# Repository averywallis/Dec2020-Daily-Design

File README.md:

# Dec2020-Daily-Design
Attempt at daily designs in December 2020. Expect very unfinished design, some with potentially massive issues

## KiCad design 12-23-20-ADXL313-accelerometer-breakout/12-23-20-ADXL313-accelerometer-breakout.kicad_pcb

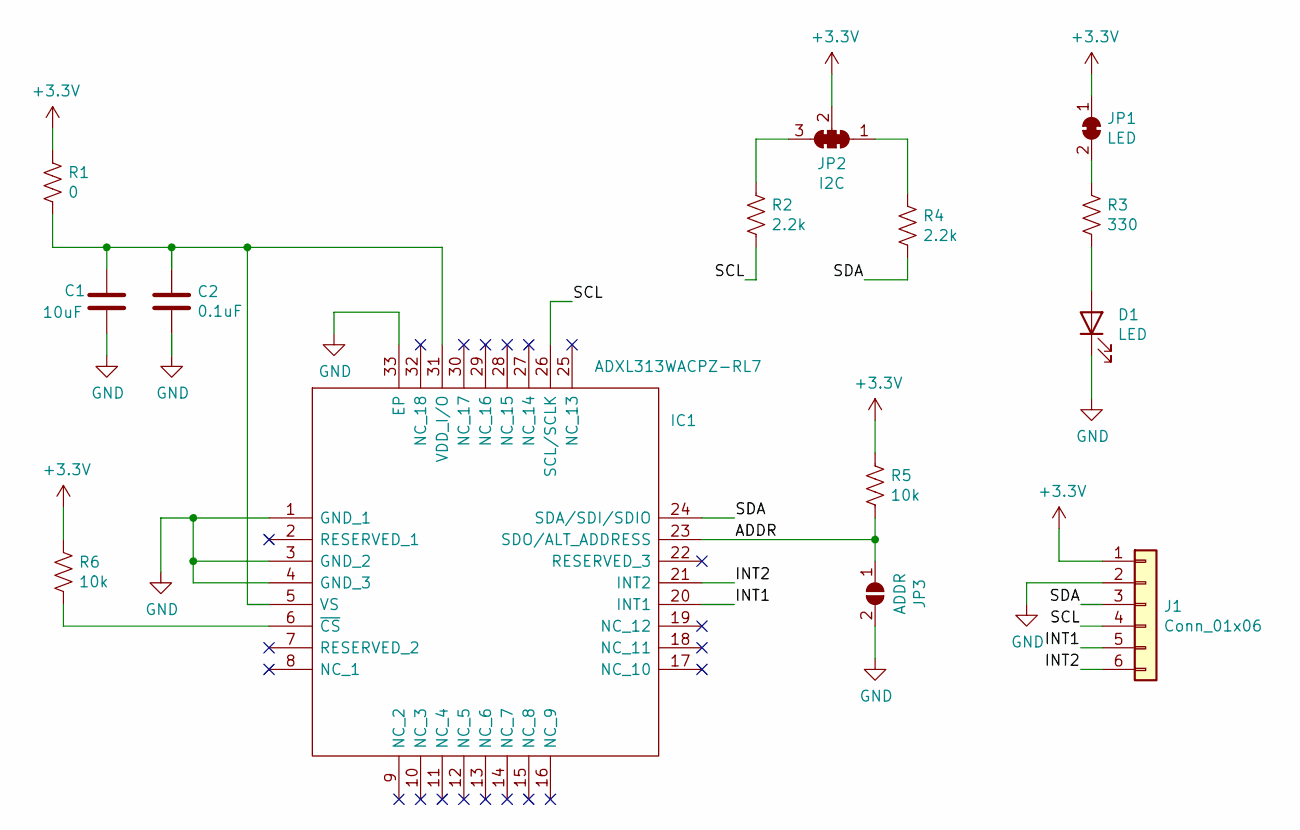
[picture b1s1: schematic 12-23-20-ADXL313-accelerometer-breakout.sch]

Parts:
C1: 10uF; C_0805_2012Metric
C2: 0.1uF; C_0805_2012Metric
D1: LED; LED_0805_2012Metric
IC1: ADXL313WACPZ-RL7; QFN50P500X500X155-33N-D; Manufacturer_Part_Number ADXL313WACPZ-RL7; Mouser Part Number 584-ADXL313WACPZ-RL7
J1: Conn_01x06; PinHeader_1x06_P2.54mm_Vertical
JP1: LED; SolderJumper-2_P1.3mm_Bridged_RoundedPad1.0x1.5mm
JP2: I2C; SMT-JUMPER_3_2-NC_TRACE_SILK
JP3: ADDR; SolderJumper-2_P1.3mm_Open_RoundedPad1.0x1.5mm
R1: 0; R_0805_2012Metric
R2, R4: 2.2k; R_0805_2012Metric
R3: 330; R_0805_2012Metric
R5, R6: 10k; R_0805_2012Metric

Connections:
+3V3: J1.1, JP1.1 (A), JP2.2 (C), R1.1, R5.1, R6.1
/ADDR: IC1.23 (SDO/ALT_ADDRESS), JP3.1 (A), R5.2
/INT1: IC1.20 (INT1), J1.5
/INT2: IC1.21 (INT2), J1.6
/SCL: IC1.26 (SCL/SCLK), J1.4, R2.2
/SDA: IC1.24 (SDA/SDI/SDIO), J1.3, R4.2
GND: C1.2, C2.2, D1.1 (K), IC1.1 (GND_1), IC1.3 (GND_2), IC1.4 (GND_3), IC1.33 (EP), J1.2, JP3.2 (B)
unnamed: C1.1, C2.1, IC1.5 (VS), IC1.31 (VDD_I/O), R1.2
unnamed: D1.2 (A), R3.2
unnamed: IC1.6 (~CS), R6.2
unnamed: JP1.2 (B), R3.1
unnamed: JP2.1 (A), R4.1
unnamed: JP2.3 (B), R2.1

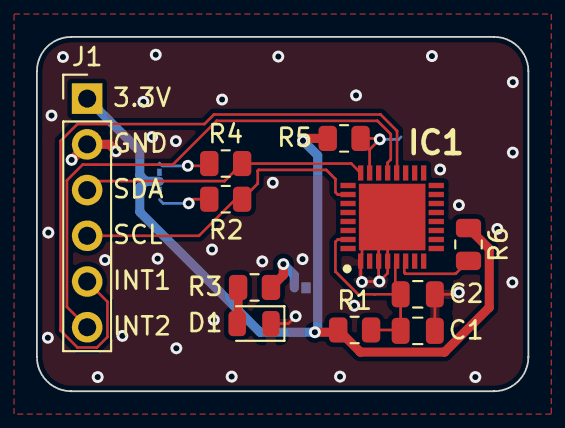
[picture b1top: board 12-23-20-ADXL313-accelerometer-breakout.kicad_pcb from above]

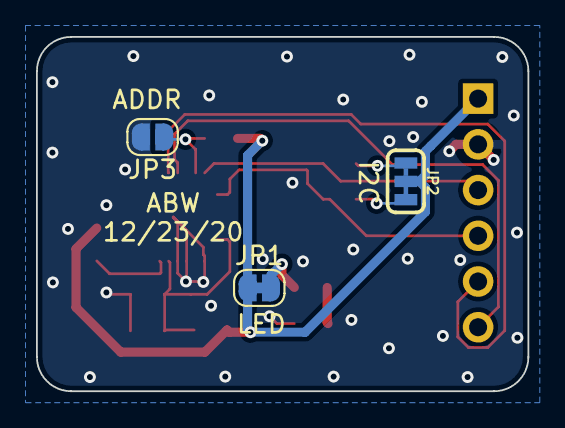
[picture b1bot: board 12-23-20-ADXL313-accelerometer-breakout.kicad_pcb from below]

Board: 2 copper layers, 27.3 x 19.7 mm, 14 parts (3 on the bottom side), 13 nets.

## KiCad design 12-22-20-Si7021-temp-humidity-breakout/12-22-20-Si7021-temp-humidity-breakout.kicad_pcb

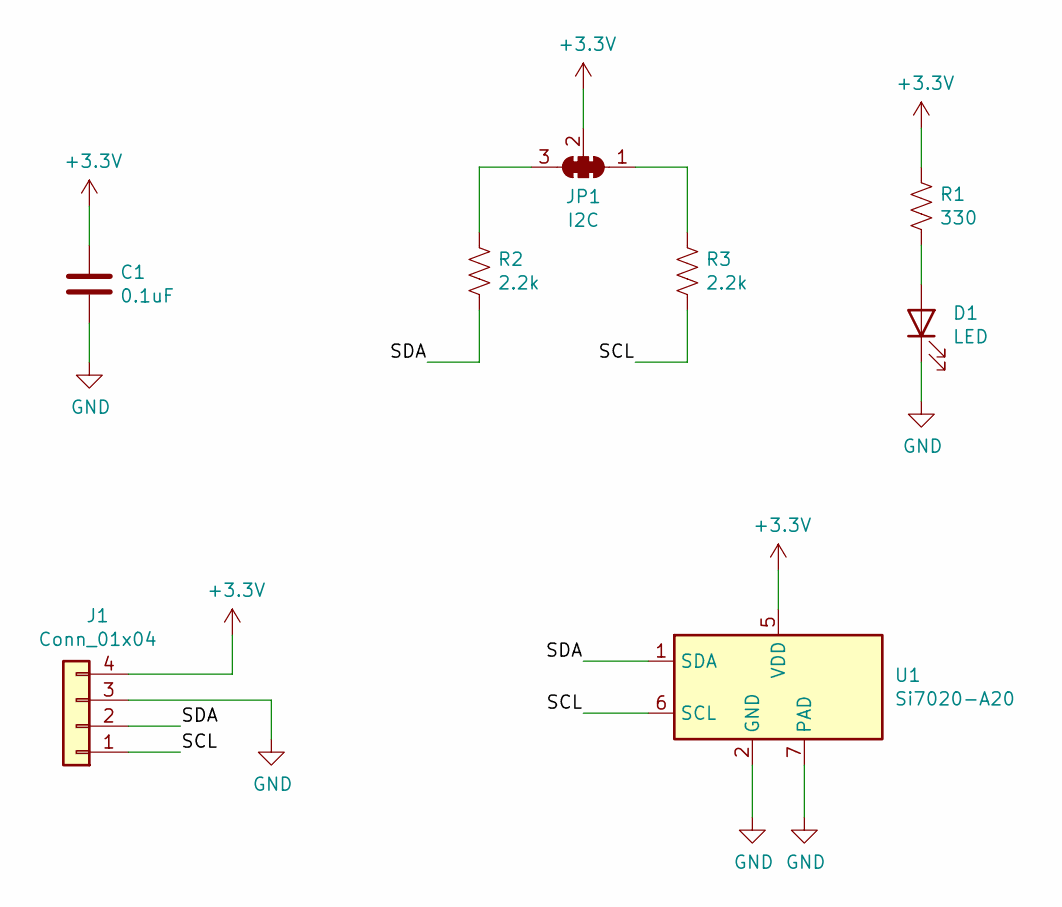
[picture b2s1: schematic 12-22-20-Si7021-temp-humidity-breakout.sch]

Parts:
C1: 0.1uF; C_0805_2012Metric
D1: LED; LED_0805_2012Metric
J1: Conn_01x04; PinHeader_1x04_P2.54mm_Vertical
JP1: I2C; SMT-JUMPER_3_2-NC_TRACE_SILK
R1: 330; R_0805_2012Metric
R2, R3: 2.2k; R_0805_2012Metric
U1: Si7020-A20; DFN-6-1EP_3x3mm_P1mm_EP1.5x2.4mm

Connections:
+3V3: C1.1, J1.4, JP1.2 (C), R1.1, U1.5 (VDD)
/SCL: J1.1, R3.2, U1.6 (SCL)
/SDA: J1.2, R2.2, U1.1 (SDA)
GND: C1.2, D1.1 (K), J1.3, U1.2 (GND), U1.7 (PAD)
unnamed: D1.2 (A), R1.2
unnamed: JP1.1 (A), R3.1
unnamed: JP1.3 (B), R2.1

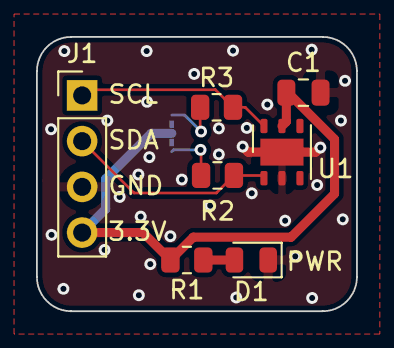
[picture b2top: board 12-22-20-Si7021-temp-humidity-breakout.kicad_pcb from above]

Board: 2 copper layers, 17.8 x 15.2 mm, 8 parts (1 on the bottom side), 7 nets.

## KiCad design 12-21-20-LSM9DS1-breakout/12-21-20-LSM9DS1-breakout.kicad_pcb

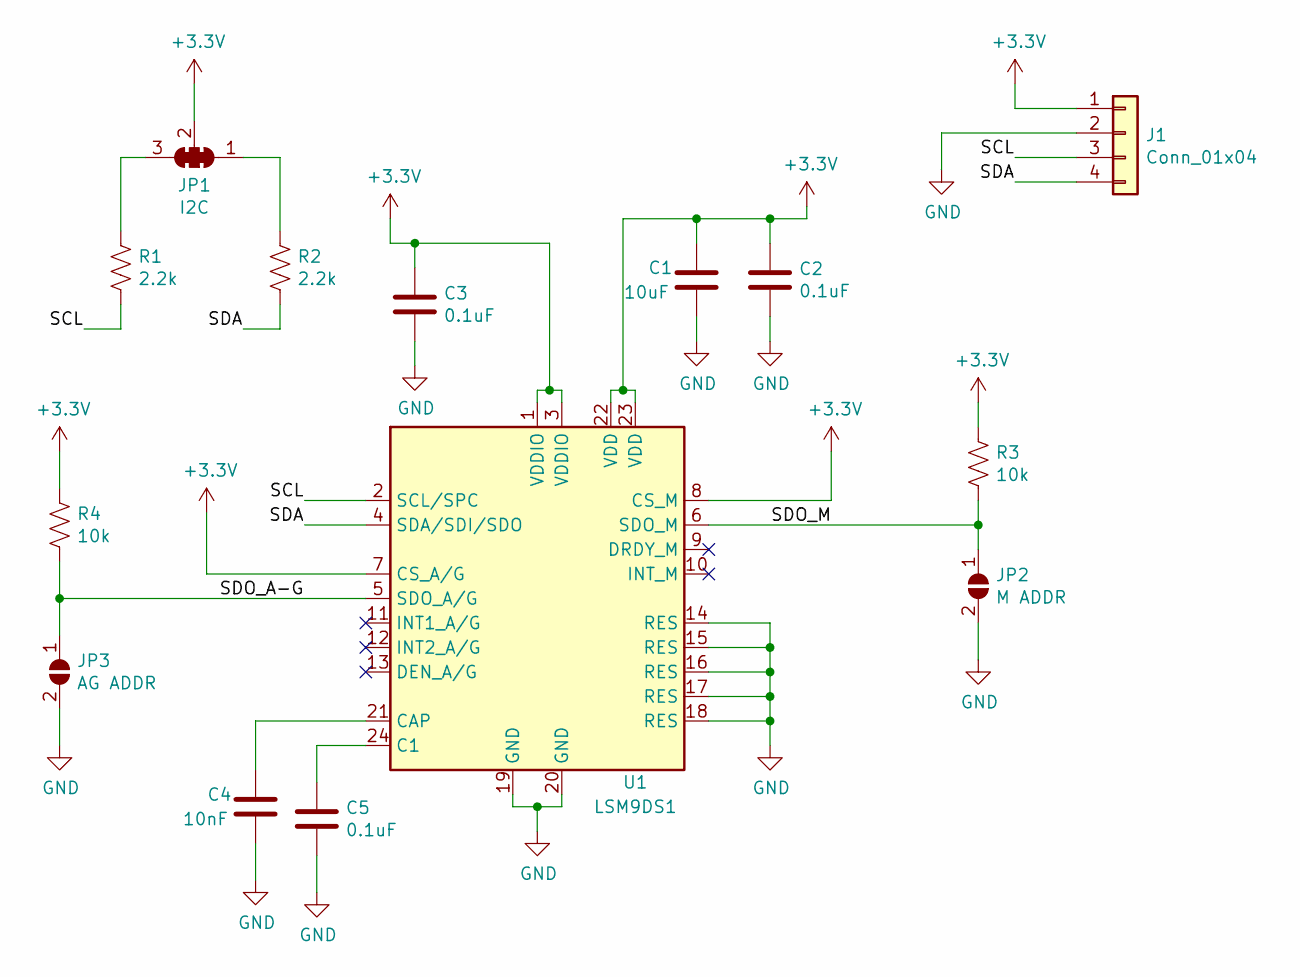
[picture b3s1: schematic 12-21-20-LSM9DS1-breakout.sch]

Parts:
C1: 10uF; C_0805_2012Metric
C2, C3, C5: 0.1uF; C_0805_2012Metric
C4: 10nF; C_0805_2012Metric
J1: Conn_01x04; PinHeader_1x04_P2.54mm_Vertical
JP1: I2C; SMT-JUMPER_3_2-NC_TRACE_SILK
JP2: M ADDR; SolderJumper-2_P1.3mm_Open_RoundedPad1.0x1.5mm
JP3: AG ADDR; SolderJumper-2_P1.3mm_Open_RoundedPad1.0x1.5mm
R1, R2: 2.2k; R_0805_2012Metric
R3, R4: 10k; R_0805_2012Metric
U1: LSM9DS1; LGA-24L_3x3.5mm_P0.43mm

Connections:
+3V3: C1.1, C2.1, C3.1, J1.1, JP1.2 (C), R3.1, R4.1, U1.1 (VDDIO), U1.3 (VDDIO), U1.7 (CS_A/G), U1.8 (CS_M), U1.22 (VDD), U1.23 (VDD)
/SCL: J1.3, R1.2, U1.2 (SCL/SPC)
/SDA: J1.4, R2.2, U1.4 (SDA/SDI/SDO)
/SDO_A-G: JP3.1 (A), R4.2, U1.5 (SDO_A/G)
/SDO_M: JP2.1 (A), R3.2, U1.6 (SDO_M)
GND: C1.2, C2.2, C3.2, C4.2, C5.2, J1.2, JP2.2 (B), JP3.2 (B), U1.14 (RES), U1.15 (RES), U1.16 (RES), U1.17 (RES), U1.18 (RES), U1.19 (GND), U1.20 (GND)
unnamed: C4.1, U1.21 (CAP)
unnamed: C5.1, U1.24 (C1)
unnamed: JP1.1 (A), R2.1
unnamed: JP1.3 (B), R1.1

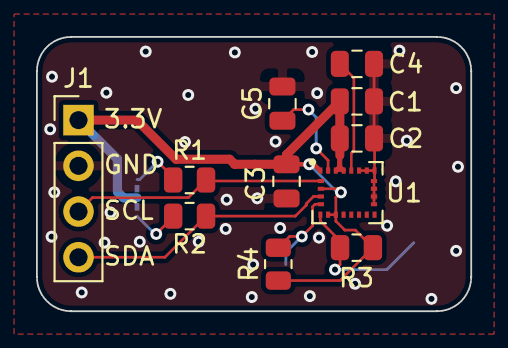
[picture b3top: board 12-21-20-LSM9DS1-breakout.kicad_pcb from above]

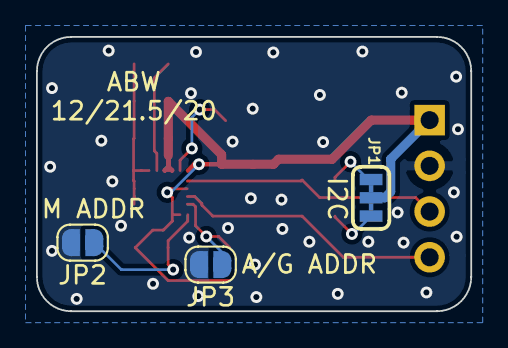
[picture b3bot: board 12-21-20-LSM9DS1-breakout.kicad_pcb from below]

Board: 2 copper layers, 24.1 x 15.2 mm, 14 parts (3 on the bottom side), 10 nets.

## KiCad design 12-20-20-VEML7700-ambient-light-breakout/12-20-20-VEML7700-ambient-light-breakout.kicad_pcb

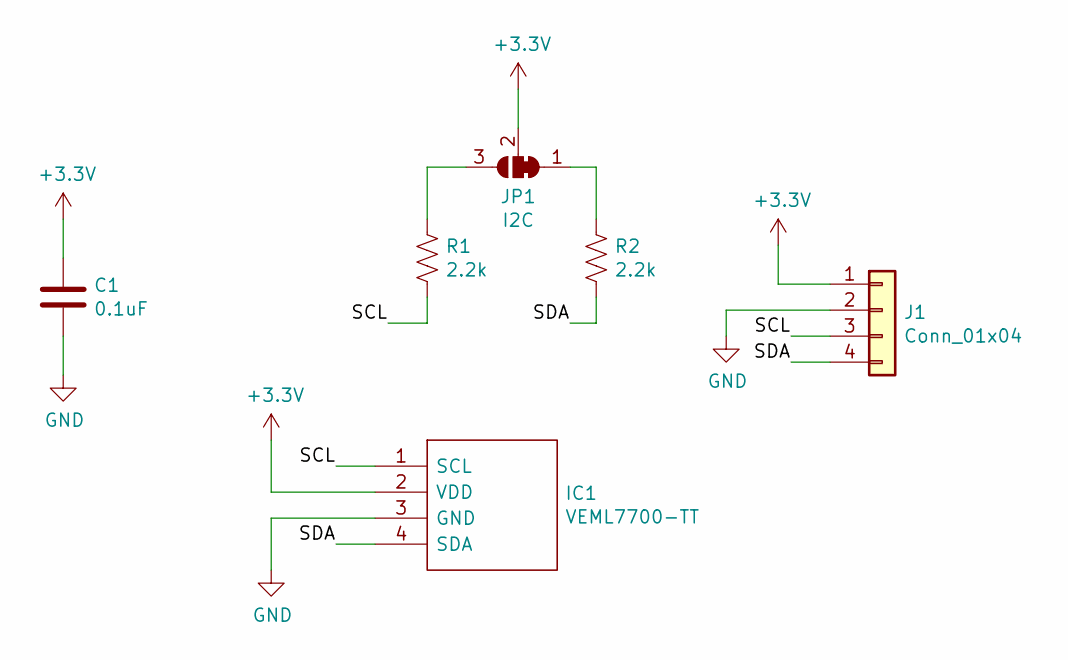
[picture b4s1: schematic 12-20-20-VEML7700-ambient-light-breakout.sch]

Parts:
C1: 0.1uF; C_0805_2012Metric
IC1: VEML7700-TT; VEML7700; Manufacturer_Part_Number VEML7700-TT; Mouser Part Number 78-VEML7700-TT
J1: Conn_01x04; PinHeader_1x04_P2.54mm_Vertical
JP1: I2C; SMT-JUMPER_3_2-NC_TRACE_SILK
R1, R2: 2.2k; R_0805_2012Metric

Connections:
+3V3: C1.1, IC1.2 (VDD), J1.1, JP1.2 (C)
/SCL: IC1.1 (SCL), J1.3, R1.2
/SDA: IC1.4 (SDA), J1.4, R2.2
GND: C1.2, IC1.3 (GND), J1.2
unnamed: JP1.1 (A), R2.1
unnamed: JP1.3 (B), R1.1

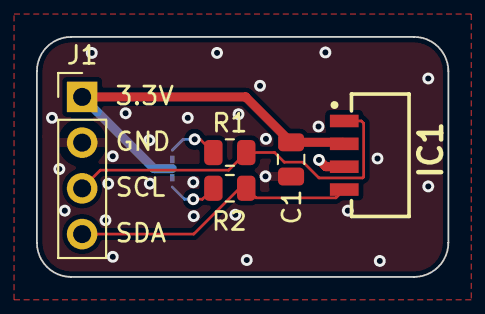
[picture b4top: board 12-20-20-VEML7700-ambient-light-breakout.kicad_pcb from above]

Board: 2 copper layers, 22.9 x 13.3 mm, 6 parts (1 on the bottom side), 6 nets.

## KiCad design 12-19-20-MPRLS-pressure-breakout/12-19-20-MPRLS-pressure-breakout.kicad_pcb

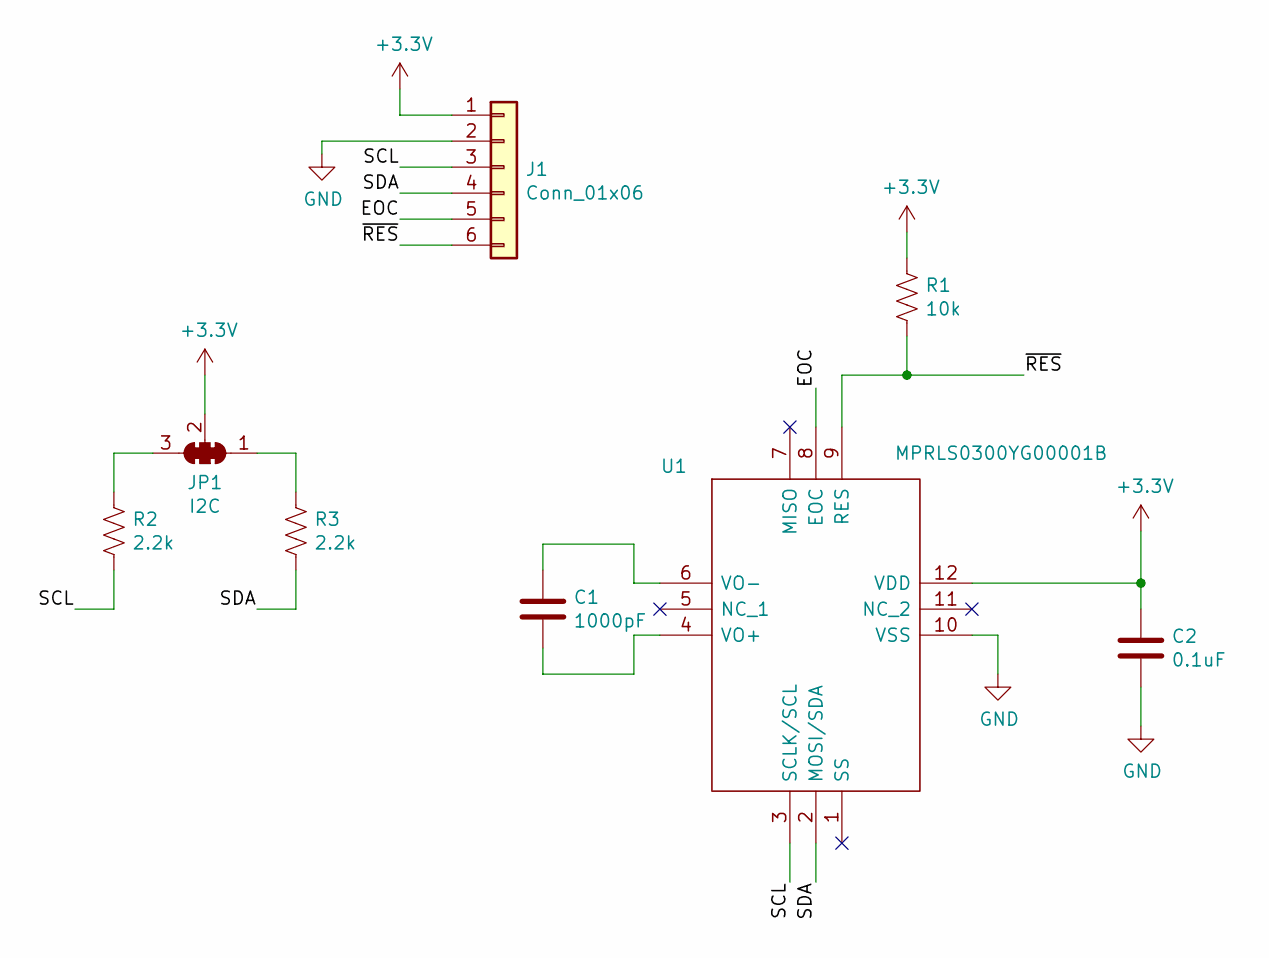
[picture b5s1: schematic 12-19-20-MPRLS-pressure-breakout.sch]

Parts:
C1: 1000pF; C_0805_2012Metric
C2: 0.1uF; C_0805_2012Metric
J1: Conn_01x06; PinHeader_1x06_P2.54mm_Vertical
JP1: I2C; SMT-JUMPER_3_2-NC_TRACE_SILK
R1: 10k; R_0805_2012Metric
R2, R3: 2.2k; R_0805_2012Metric
U1: MPRLS0300YG00001B; Manufacturer_Part_Number MPRLS0300YG00001B; Mouser Part Number 785-MPRLS0300YG0001B

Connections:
+3V3: C2.1, J1.1, JP1.2 (C), R1.1, U1.12 (VDD)
/EOC: J1.5, U1.8 (EOC)
/SCL: J1.3, R2.2, U1.3 (SCLK/SCL)
/SDA: J1.4, R3.2, U1.2 (MOSI/SDA)
/~RES: J1.6, R1.2, U1.9 (RES)
GND: C2.2, J1.2, U1.10 (VSS)
unnamed: C1.1, U1.6 (VO-)
unnamed: C1.2, U1.4 (VO+)
unnamed: JP1.1 (A), R3.1
unnamed: JP1.3 (B), R2.1

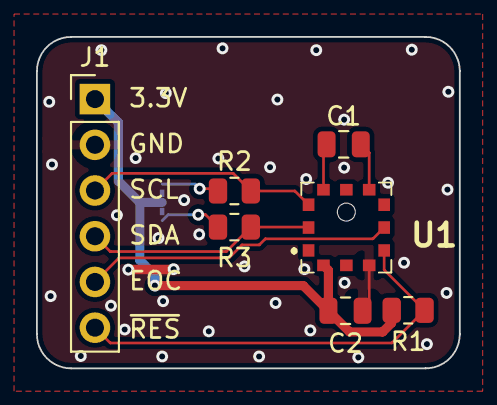
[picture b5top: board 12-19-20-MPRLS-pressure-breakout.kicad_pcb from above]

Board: 2 copper layers, 23.5 x 18.4 mm, 8 parts (1 on the bottom side), 10 nets.

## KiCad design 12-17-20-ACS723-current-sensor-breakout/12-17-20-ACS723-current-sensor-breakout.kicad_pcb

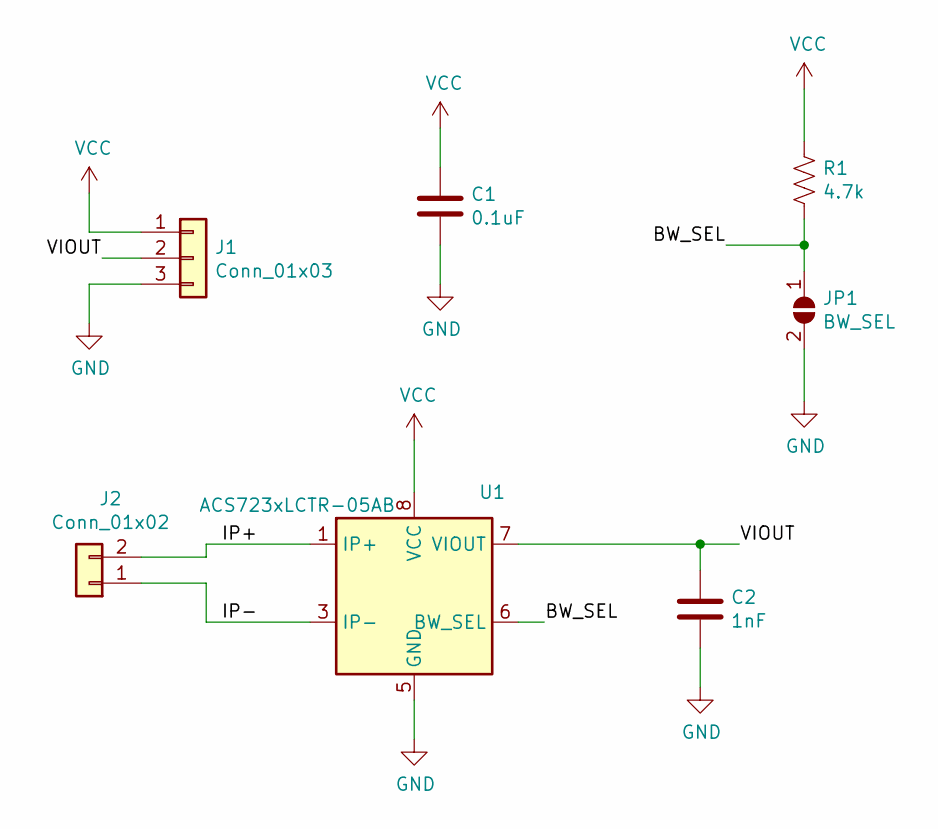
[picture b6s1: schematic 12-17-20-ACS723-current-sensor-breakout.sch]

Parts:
C1: 0.1uF; C_0805_2012Metric
C2: 1nF; C_0805_2012Metric
J1: Conn_01x03; PinHeader_1x03_P2.54mm_Vertical
J2: Conn_01x02; PinHeader_1x02_P2.54mm_Vertical
JP1: BW_SEL; SolderJumper-2_P1.3mm_Open_RoundedPad1.0x1.5mm
R1: 4.7k; R_0805_2012Metric
U1: ACS723xLCTR-05AB; SOIC-8_3.9x4.9mm_P1.27mm

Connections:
/BW_SEL: JP1.1 (A), R1.2, U1.6 (BW_SEL)
/IP+: J2.2, U1.1 (IP+), U1.2 (IP+)
/IP-: J2.1, U1.3 (IP-), U1.4 (IP-)
/VIOUT: C2.1, J1.2, U1.7 (VIOUT)
GND: C1.2, C2.2, J1.3, JP1.2 (B), U1.5 (GND)
VCC: C1.1, J1.1, R1.1, U1.8 (VCC)

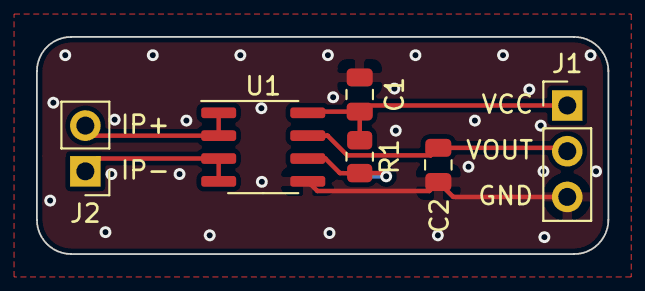
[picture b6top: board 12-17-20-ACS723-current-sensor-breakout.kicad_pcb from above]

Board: 2 copper layers, 31.8 x 12.1 mm, 7 parts (1 on the bottom side), 6 nets.

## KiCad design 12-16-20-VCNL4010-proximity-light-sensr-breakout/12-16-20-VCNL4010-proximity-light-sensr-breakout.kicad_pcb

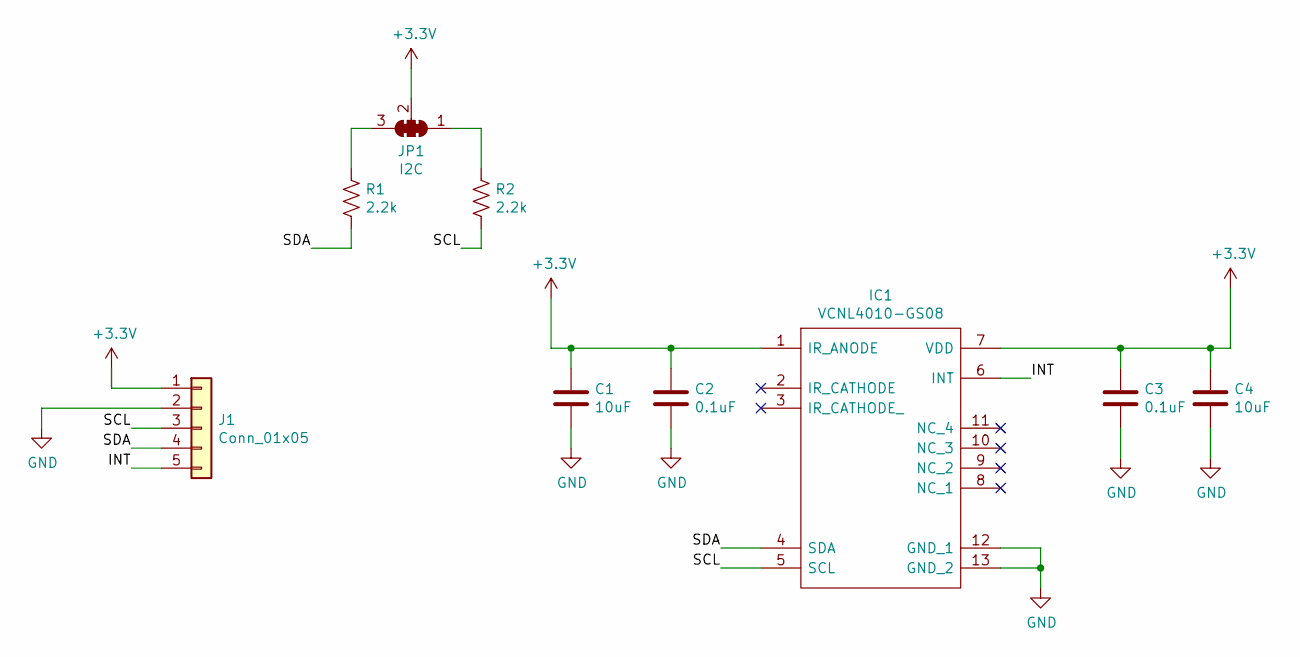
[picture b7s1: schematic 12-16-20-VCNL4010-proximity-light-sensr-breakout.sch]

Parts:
C1, C4: 10uF; C_0805_2012Metric
C2, C3: 0.1uF; C_0805_2012Metric
IC1: VCNL4010-GS08; VCNL4010GS08; Manufacturer_Part_Number VCNL4010-GS08; Mouser Part Number 78-VCNL4010-GS08
J1: Conn_01x05; PinHeader_1x05_P2.54mm_Vertical
JP1: I2C; SMT-JUMPER_3_2-NC_TRACE_SILK
R1, R2: 2.2k; R_0805_2012Metric

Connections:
+3V3: C1.1, C2.1, C3.1, C4.1, IC1.1 (IR_ANODE), IC1.7 (VDD), J1.1, JP1.2 (C)
/INT: IC1.6 (INT), J1.5
/SCL: IC1.5 (SCL), J1.3, R2.2
/SDA: IC1.4 (SDA), J1.4, R1.2
GND: C1.2, C2.2, C3.2, C4.2, IC1.12 (GND_1), IC1.13 (GND_2), J1.2
unnamed: JP1.1 (A), R2.1
unnamed: JP1.3 (B), R1.1

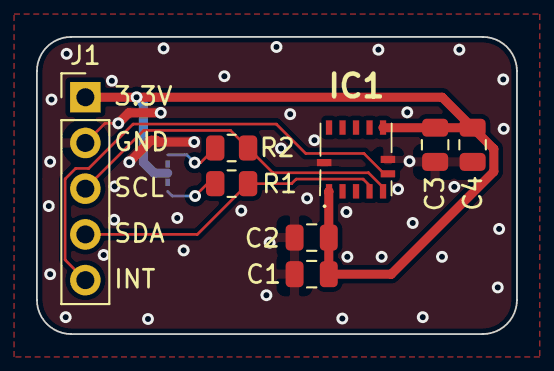
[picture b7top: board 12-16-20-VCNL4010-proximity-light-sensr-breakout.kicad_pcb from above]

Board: 2 copper layers, 26.7 x 16.5 mm, 9 parts (1 on the bottom side), 7 nets.

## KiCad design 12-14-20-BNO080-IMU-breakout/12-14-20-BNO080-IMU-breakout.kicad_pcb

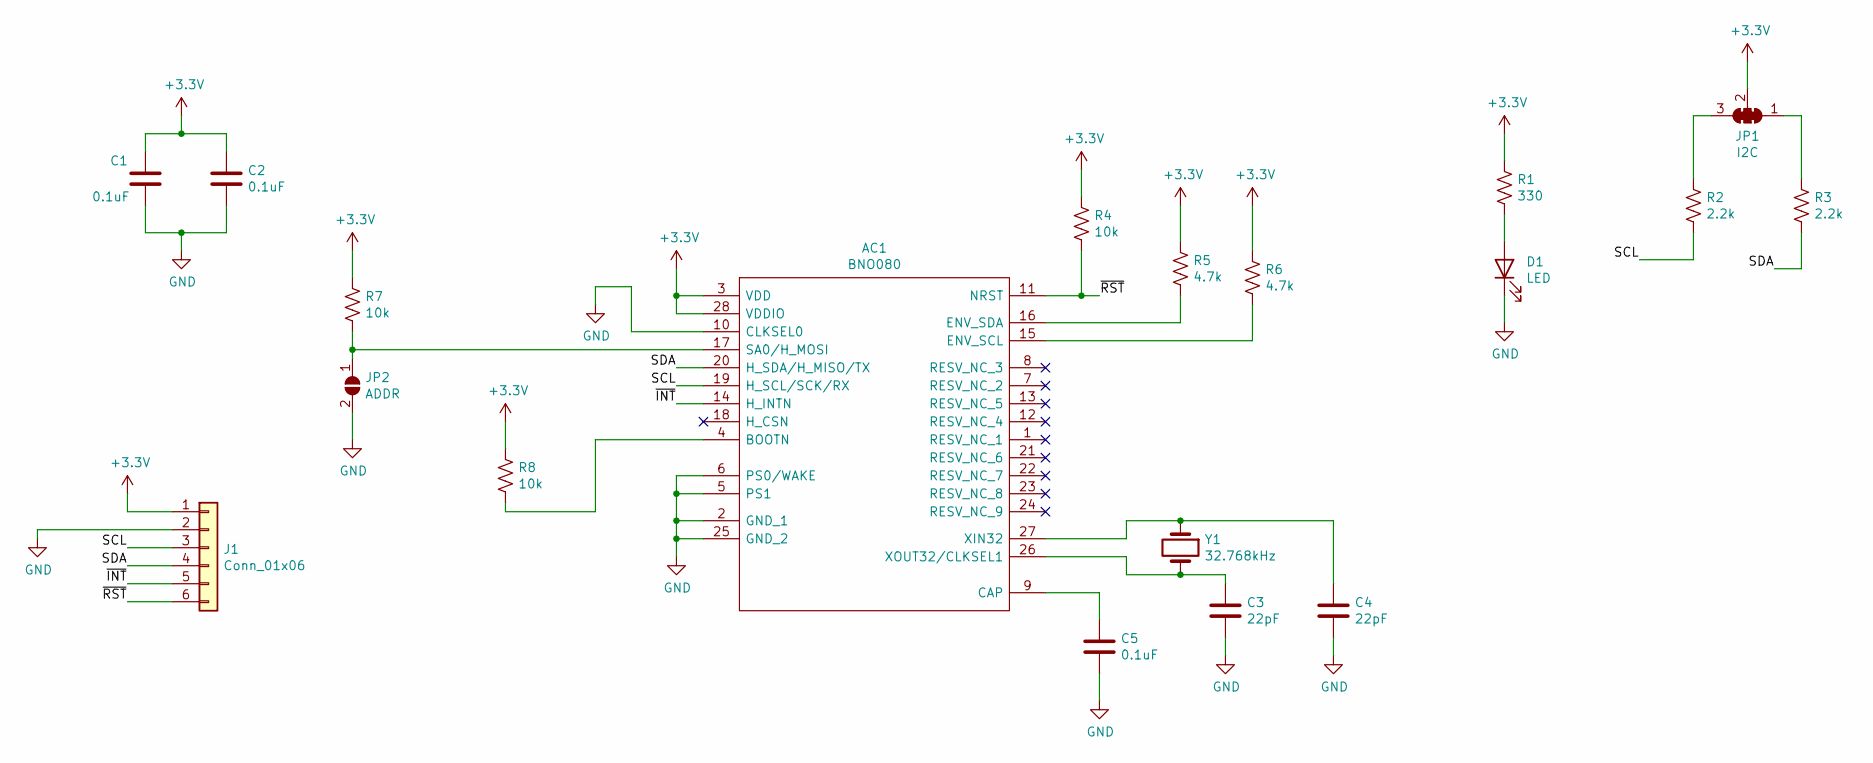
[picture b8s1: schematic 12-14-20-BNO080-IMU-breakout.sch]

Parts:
AC1: BNO080; Manufacturer_Part_Number BNO080
C1, C2, C5: 0.1uF; C_0805_2012Metric
C3, C4: 22pF; C_0805_2012Metric
D1: LED; LED_0805_2012Metric
J1: Conn_01x06; PinHeader_1x06_P2.54mm_Vertical
JP1: I2C; SMT-JUMPER_3_2-NC_TRACE_SILK
JP2: ADDR; SolderJumper-2_P1.3mm_Open_RoundedPad1.0x1.5mm
R1: 330; R_0805_2012Metric
R2, R3: 2.2k; R_0805_2012Metric
R4, R7, R8: 10k; R_0805_2012Metric
R5, R6: 4.7k; R_0805_2012Metric
Y1: 32.768kHz; Crystal_SMD_MicroCrystal_CC8V-T1A-2Pin_2.0x1.2mm

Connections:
+3V3: AC1.3 (VDD), AC1.28 (VDDIO), C1.1, C2.1, J1.1, JP1.2 (C), R1.1, R4.1, R5.1, R6.1, R7.1, R8.1
/SCL: AC1.19 (H_SCL/SCK/RX), J1.3, R2.2
/SDA: AC1.20 (H_SDA/H_MISO/TX), J1.4, R3.2
/~INT: AC1.14 (H_INTN), J1.5
/~RST: AC1.11 (NRST), J1.6, R4.2
GND: AC1.2 (GND_1), AC1.5 (PS1), AC1.6 (PS0/WAKE), AC1.10 (CLKSEL0), AC1.25 (GND_2), C1.2, C2.2, C3.2, C4.2, C5.2, D1.1 (K), J1.2, JP2.2 (B)
unnamed: AC1.4 (BOOTN), R8.2
unnamed: AC1.9 (CAP), C5.1
unnamed: AC1.15 (ENV_SCL), R6.2
unnamed: AC1.16 (ENV_SDA), R5.2
unnamed: AC1.17 (SA0/H_MOSI), JP2.1 (A), R7.2
unnamed: AC1.26 (XOUT32/CLKSEL1), C3.1, Y1.2
unnamed: AC1.27 (XIN32), C4.1, Y1.1
unnamed: D1.2 (A), R1.2
unnamed: JP1.1 (A), R3.1
unnamed: JP1.3 (B), R2.1

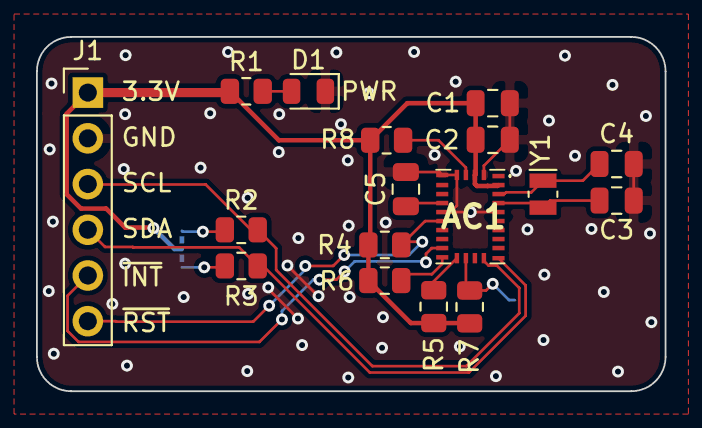
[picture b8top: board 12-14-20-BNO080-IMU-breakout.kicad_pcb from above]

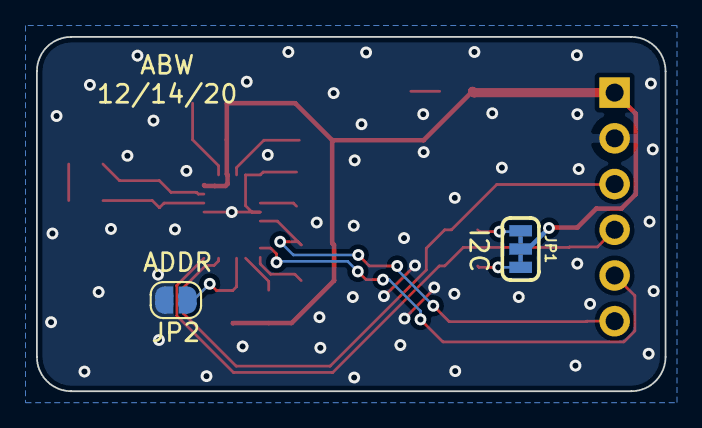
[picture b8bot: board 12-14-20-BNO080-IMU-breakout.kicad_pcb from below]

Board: 2 copper layers, 34.9 x 19.7 mm, 19 parts (2 on the bottom side), 16 nets.

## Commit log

2020-12-02 Day 1
    Day 1 Daily PCB Design: GPS Datalogger, SAMD21G18A logs GPS data from SAM-M8Q GPS module
2020-12-02 Day 2 of Daily Design: ADXL345
    A small ADXL345 accelerometer breakout board, designed for use via I2C
2020-12-03 12/3/20 daily design
    A BME680 breakout board: measure temperature, pressure, humidity, and gasses
2020-12-04 12/4/20 design
    New design expands on yesterdays design, adding a CCS811 volatile organic compound and CO2 sensor. Combined with the BME680, this board can measure most desireable environmental factors
2020-12-05 12/5/20 daily design
    Pulse oximeter breakout board. Uses MAX30101 pulse oximeter module. WEatned to implement the MAX32664 biometric sensor hub, but didn't want to spend the time implementing the design rules to implemen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
2020-12-06 12/6/20 daily design
    MS5803-14BA pressure sensor breakout board. Designed to be used with 3.3V MCU via I2C
2020-12-07 12/7/20 daily design
    TMP117 temperature sensor breakout board. Some design considerations not addressed, like sensor isolation/pcb cutaways for thermal isolation
2020-12-08 12/8/20 Daily design
    MPU 6050 triple axis accelerometer and gyro sensor breakout board. Can be paired with external sensors for additional functionality
2020-12-09 12/9/20 daily design
    TCS34725 color sensor breakout board. Designed for 3.3V MCU via I2c. Includes on-board white LED for light reflection off object you wish to detect the color of
2020-12-10 12/10/20 daily design
    A VL53L1 distance sensor breakout. THe VL53L1 is a Time of Flight sensor and can be used to detect objects up to 4 meters away. Designed for use with a 3.3V MCU via I2C
2020-12-11 12/11/20 daily design
    SGP30 gas sensor breakout board. Designed for 3.3V MCU via I2C. Pretty simple design cause finals are a thing
2020-12-13 12/12/20 Daily Design
    LIS3DH accelerometer breakout board. Designed for use with a 3.3V MCU via I2C
2020-12-14 12/13/20 daily design
    MLX90614 IR thermometer breakout board. Designed for use iwth 3.3V MCU via I2C. Pretty simple design
2020-12-14 12/14/20 daily design
    BNO080 IMU breakout board. Designed for use with 3.3V MCU via I2C
2020-12-15 12/15/20 daily design
    MLX90640 IR thermal camera breakout board. Designed for use with 3.3V MCU via I2C. Very minimalistic design
2020-12-16 12/16/20 daily design
    VCNL4010 proximity/light sensor breakout board. Designed for use with 3.3V MCU via I2C
2020-12-18 12/17/20 daily design
    ACS723 current sensor. Supply with 4.5-5.5V on Vcc, measures currents +/-5A passing through IP+ and IP-. Analog output, with sinsitivity of 400mV/A
2020-12-18 12/18/20 daily design
    AMG883 IR array breakout. Designed for use with 3.3V MCU via I2C
2020-12-19 12/19/20 daily design
    MPRLS pressure sensor breakout board. Designed for use with 3.3V MCU via I2C
2020-12-20 12/20/20 daily design
    VEML7700 ambient light sensor brekaout board. Designed for use wiht 3.3V MCU via I2C
2020-12-22 12/21.5/20
    LSM9DS1 9-DOF IMU breakout board. Designed for use with 3.3V MCU via I2C. Designed schematic yesterday but never got around to designing layout until today
2020-12-22 12/22/20 daily design
    Si7021 temperature and humidity sensor breakout board. Designed for use with 3.3V MCU via I2C
2020-12-23 12/23/20 daily design
    ADXL313 3-axis accelerometer breakout board. Designed for use with 3.3V MCU via I2C
